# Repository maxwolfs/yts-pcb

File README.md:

# yts-pcb
pcb for keyboard hardware controller for yts

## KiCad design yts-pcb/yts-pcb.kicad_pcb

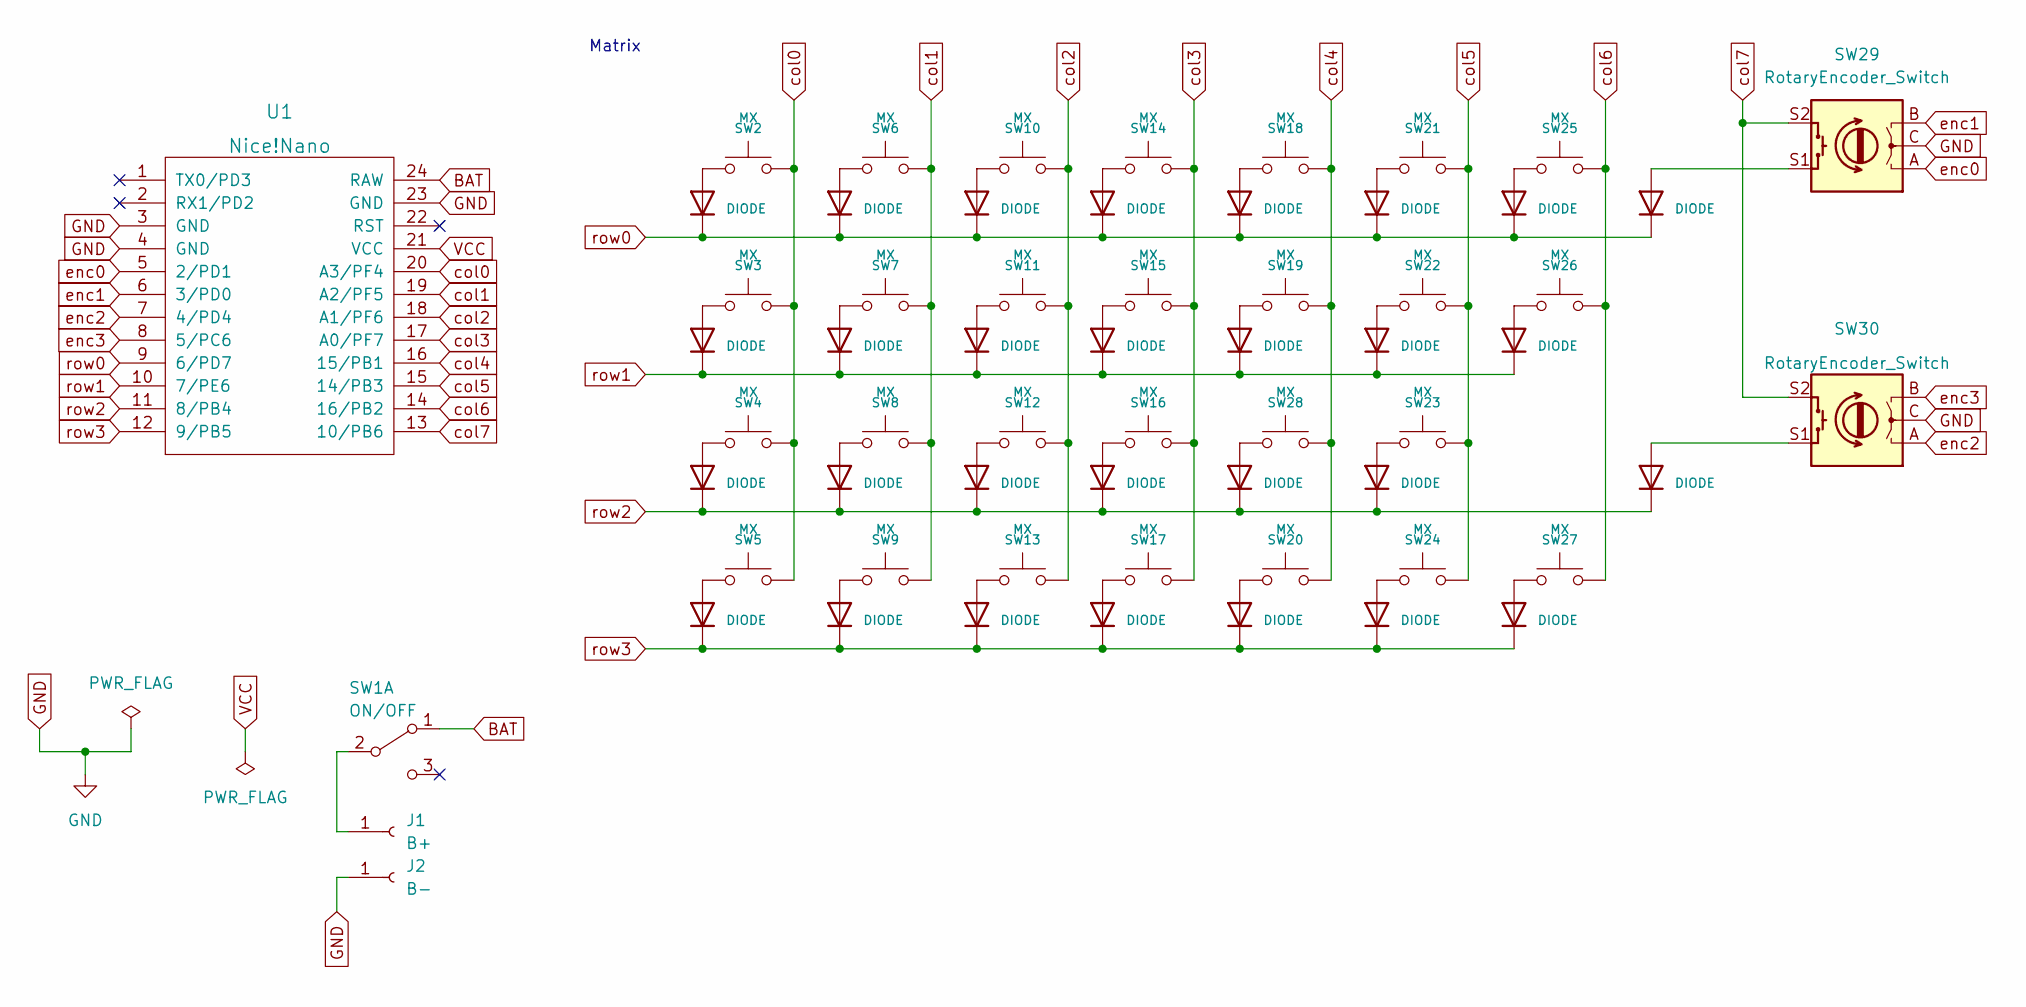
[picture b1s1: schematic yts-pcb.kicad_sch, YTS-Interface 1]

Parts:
D1, D2, D3, D4, D5, D6, D7, D8, D9, D10, D11, D12, D13, D14, D15, D16, D17, D18, D19, D20, D21, D22, D23, D24, D25, D26, D27, D28, D29: DIODE; Diode-Hybrid-Back
J1: B+; SolderWirePad_1x01_SMD_1x2mm
J2: B-; SolderWirePad_1x01_SMD_1x2mm
SW1: ON/OFF; SW_SPDT_PCM12
SW2, SW3, SW4, SW5, SW6, SW7, SW8, SW9, SW10, SW11, SW12, SW13, SW14, SW15, SW16, SW17, SW18, SW19, SW20, SW21, SW22, SW23, SW24, SW25, SW26, SW27, SW28: MX; SW_Cherry_MX_1.00u_Plate
SW29, SW30: RotaryEncoder_Switch; RotaryEncoder_EC11
U1: Nice!Nano; ArduinoProMicro-BackSide

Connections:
BAT: SW1.1 (A), U1.24 (RAW)
GND: J2.1, SW29.C, SW30.C, U1.3 (GND), U1.4 (GND), U1.23 (GND)
unnamed: D1.1 (A), SW2.1
unnamed: D2.1 (A), SW3.1
unnamed: D3.1 (A), SW4.1
unnamed: D4.1 (A), SW5.1
unnamed: D5.1 (A), SW6.1
unnamed: D6.1 (A), SW7.1
unnamed: D7.1 (A), SW8.1
unnamed: D8.1 (A), SW9.1
unnamed: D9.1 (A), SW10.1
unnamed: D10.1 (A), SW11.1
unnamed: D11.1 (A), SW12.1
unnamed: D12.1 (A), SW13.1
unnamed: D13.1 (A), SW14.1
unnamed: D14.1 (A), SW15.1
unnamed: D15.1 (A), SW16.1
unnamed: D16.1 (A), SW17.1
unnamed: D17.1 (A), SW18.1
unnamed: D18.1 (A), SW19.1
unnamed: D19.1 (A), SW20.1
unnamed: D20.1 (A), SW21.1
unnamed: D21.1 (A), SW22.1
unnamed: D22.1 (A), SW23.1
unnamed: D23.1 (A), SW24.1
unnamed: D24.1 (A), SW25.1
unnamed: D25.1 (A), SW26.1
unnamed: D26.1 (A), SW27.1
unnamed: D27.1 (A), SW29.S1
unnamed: D28.1 (A), SW28.1
unnamed: D29.1 (A), SW30.S1
unnamed: J1.1, SW1.2 (B)
VCC: U1.21 (VCC)
col0: SW2.2, SW3.2, SW4.2, SW5.2, U1.20 (A3/PF4)
col1: SW6.2, SW7.2, SW8.2, SW9.2, U1.19 (A2/PF5)
col2: SW10.2, SW11.2, SW12.2, SW13.2, U1.18 (A1/PF6)
col3: SW14.2, SW15.2, SW16.2, SW17.2, U1.17 (A0/PF7)
col4: SW18.2, SW19.2, SW20.2, SW28.2, U1.16 (15/PB1)
col5: SW21.2, SW22.2, SW23.2, SW24.2, U1.15 (14/PB3)
col6: SW25.2, SW26.2, SW27.2, U1.14 (16/PB2)
col7: SW29.S2, SW30.S2, U1.13 (10/PB6)
enc0: SW29.A, U1.5 (2/PD1)
enc1: SW29.B, U1.6 (3/PD0)
enc2: SW30.A, U1.7 (4/PD4)
enc3: SW30.B, U1.8 (5/PC6)
row0: D1.2 (K), D5.2 (K), D9.2 (K), D13.2 (K), D17.2 (K), D20.2 (K), D24.2 (K), D27.2 (K), U1.9 (6/PD7)
row1: D2.2 (K), D6.2 (K), D10.2 (K), D14.2 (K), D18.2 (K), D21.2 (K), D25.2 (K), U1.10 (7/PE6)
row2: D3.2 (K), D7.2 (K), D11.2 (K), D15.2 (K), D22.2 (K), D28.2 (K), D29.2 (K), U1.11 (8/PB4)
row3: D4.2 (K), D8.2 (K), D12.2 (K), D16.2 (K), D19.2 (K), D23.2 (K), D26.2 (K), U1.12 (9/PB5)

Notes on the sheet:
Matrix

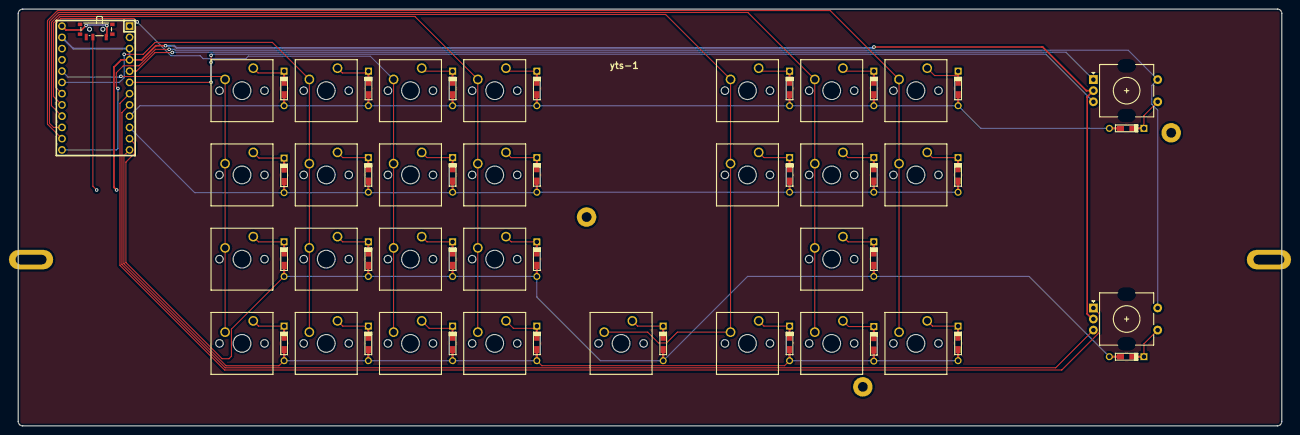
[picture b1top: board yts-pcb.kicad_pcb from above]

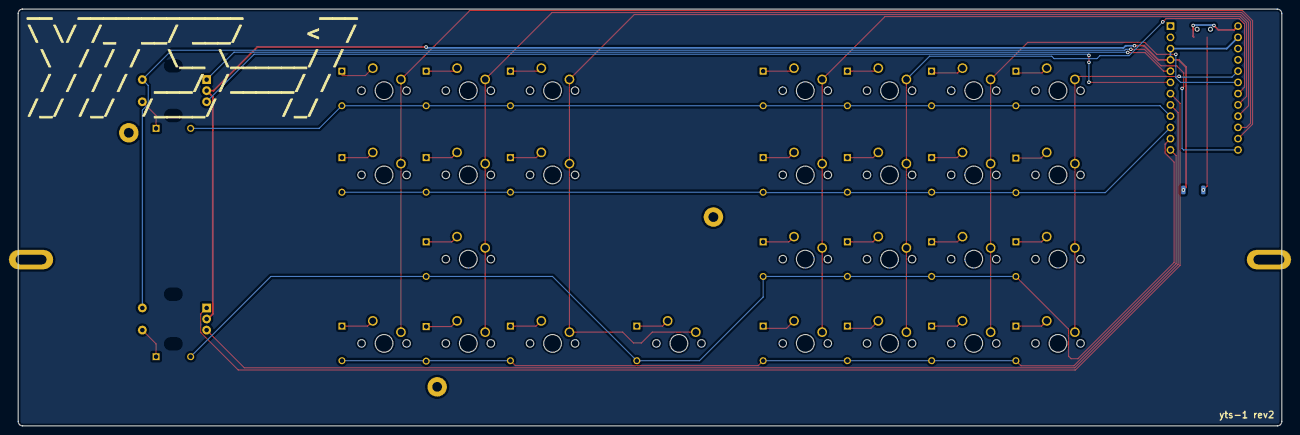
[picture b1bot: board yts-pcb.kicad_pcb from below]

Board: 2 copper layers, 285.0 x 94.0 mm, 62 parts (32 on the bottom side), 48 nets.

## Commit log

2022-09-10 init schematics
2022-09-10 add symbol and footprint libs
2022-09-11 finish schematics
2022-09-11 finish schematics and footprints
2022-09-12 finish pcb layout
2022-09-12 init switchblade
2022-09-12 update switchblade
2022-09-13 update mx switches footprints to plate mount
2022-09-13 update 3d models
2022-09-13 update footprints
2022-09-14 make gerbers rev0
2022-09-14 update pcb
2022-09-15 fix dimensions
2022-09-15 add mounting holes
2022-09-15 correct measurements
2022-09-15 finish rev1
2022-09-16 add 3d models for presentation
2022-09-17 fix 3dmodel alignment
2022-09-22 fix switchplate rev1 dimensions
2022-09-22 update dimensions rev2
2022-10-08 move silkscreen descriptions to fab layer
2022-10-08 add all mounting holes and mcu to left side
2022-10-11 fix layout
2022-10-11 update dimensions
2022-10-11 fix height
2022-10-11 finish rev2 and generate gerbers
2022-10-11 add gerbers rev2
2023-02-18 add keyboard matrix code
